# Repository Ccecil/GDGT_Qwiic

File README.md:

Simple breakout board for the Smoothieboard V2 which converts Gadgeteer I2C to the Qwiic standard.

Schematic here: [GDGT_Qwiic.pdf](https://github.com/user-attachments/files/24162902/GDGT_Qwiic.pdf)

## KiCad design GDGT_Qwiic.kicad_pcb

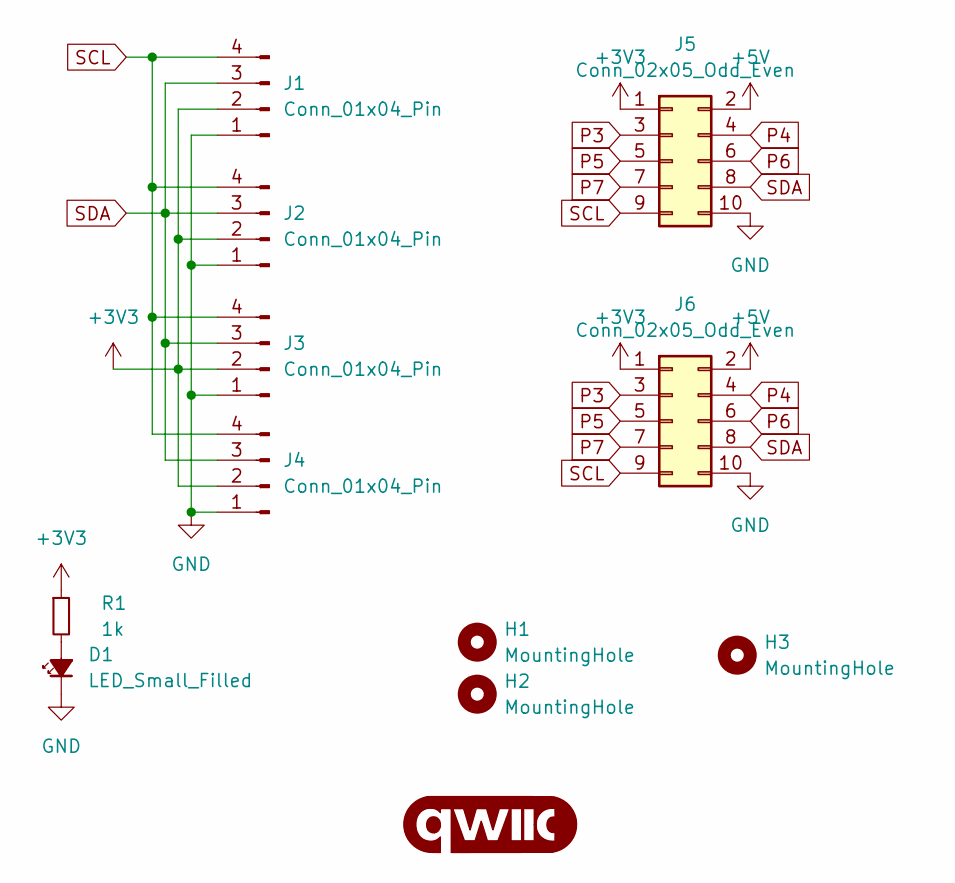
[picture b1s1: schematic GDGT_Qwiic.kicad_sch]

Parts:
D1: LED_Small_Filled; LED_0603_1608Metric
G1: qwiic_Logo; qwiic_4mm
H1, H2: MountingHole; MountingHole_3.2mm_M3
H3: MountingHole; MountingHole_2.5mm
J1, J2, J3, J4: Conn_01x04_Pin; JST_SH_SM04B-SRSS-TB_1x04-1MP_P1.00mm_Horizontal
J5, J6: Conn_02x05_Odd_Even; PinHeader_2x05_P1.27mm_Vertical_SMD
R1: 1k; R_0402_1005Metric_Pad0.72x0.64mm_HandSolder

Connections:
+3V3: J1.2, J2.2, J3.2, J4.2, J5.1, J6.1, R1.1
+5V: J5.2, J6.2
GND: D1.1 (K), J1.1, J2.1, J3.1, J4.1, J5.10, J6.10
unnamed: D1.2 (A), R1.2
P3: J5.3, J6.3
P4: J5.4, J6.4
P5: J5.5, J6.5
P6: J5.6, J6.6
P7: J5.7, J6.7
SCL: J1.4, J2.4, J3.4, J4.4, J5.9, J6.9
SDA: J1.3, J2.3, J3.3, J4.3, J5.8, J6.8

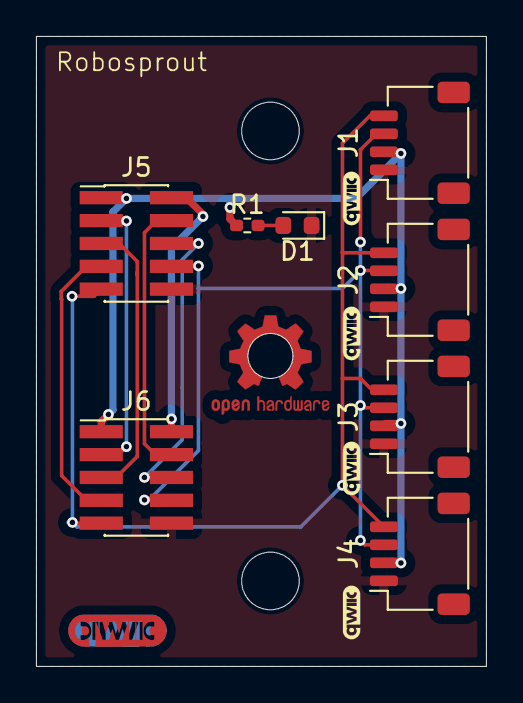
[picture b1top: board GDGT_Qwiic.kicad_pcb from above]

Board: 2 copper layers, 25.0 x 35.0 mm, 11 parts (0 on the bottom side), 11 nets.
